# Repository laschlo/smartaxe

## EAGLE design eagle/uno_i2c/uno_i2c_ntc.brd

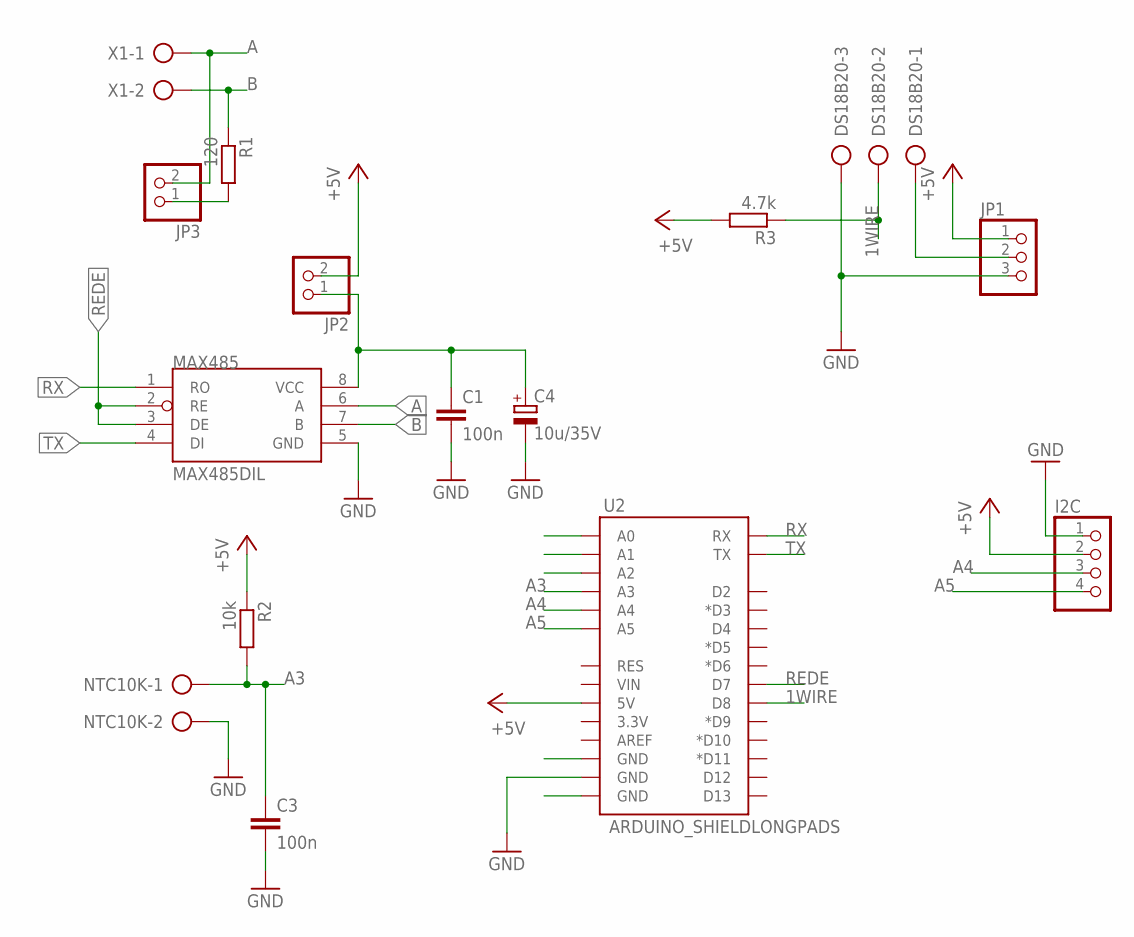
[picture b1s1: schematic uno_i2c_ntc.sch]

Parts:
C1, C3: 100n; C025-024X044
C4: 10u/35V; E2,5-5
DS18B20: AK500/3
I2C: PINHD-1X4/90; 1X04/90
JP1: PINHD-1X3; 1X03
JP2, JP3: PINHD-1X2; 1X02
MAX485: MAX485DIL; DIL08
NTC10K: AK500/2
R1: 120; 0207/10
R2: 10k; 0207/10
R3: 4.7k; 0207/10
U2: ARDUINO_SHIELDLONGPADS; DUEMILANOVE_SHIELD_LONGPADS
X1: AK500/2

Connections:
1WIRE: DS18B20.2, R3.1, U2.D8
+5V: I2C.2, JP1.1, JP2.2, R2.1, R3.2, U2.5V
A: JP3.2, MAX485.6 (A), X1.1
A0: U2.A0
A1: U2.A1
A2: U2.A2
A3: C3.1, NTC10K.1, R2.2, U2.A3
A4: I2C.3, U2.A4
A5: I2C.4, U2.A5
B: MAX485.7 (B), R1.1, X1.2
GND: C1.2, C3.2, C4.-, DS18B20.3, I2C.1, JP1.3, MAX485.5 (GND), NTC10K.2, U2.GND@0 (GND), U2.GND@1 (GND), U2.GND@2 (GND)
unnamed: JP3.1, R1.2
unnamed: DS18B20.1, JP1.2
unnamed: C1.1, C4.+, JP2.1, MAX485.8 (VCC)
REDE: MAX485.2 (RE), MAX485.3 (DE), U2.D7
RX: MAX485.1 (RO), U2.RX
TX: MAX485.4 (DI), U2.TX

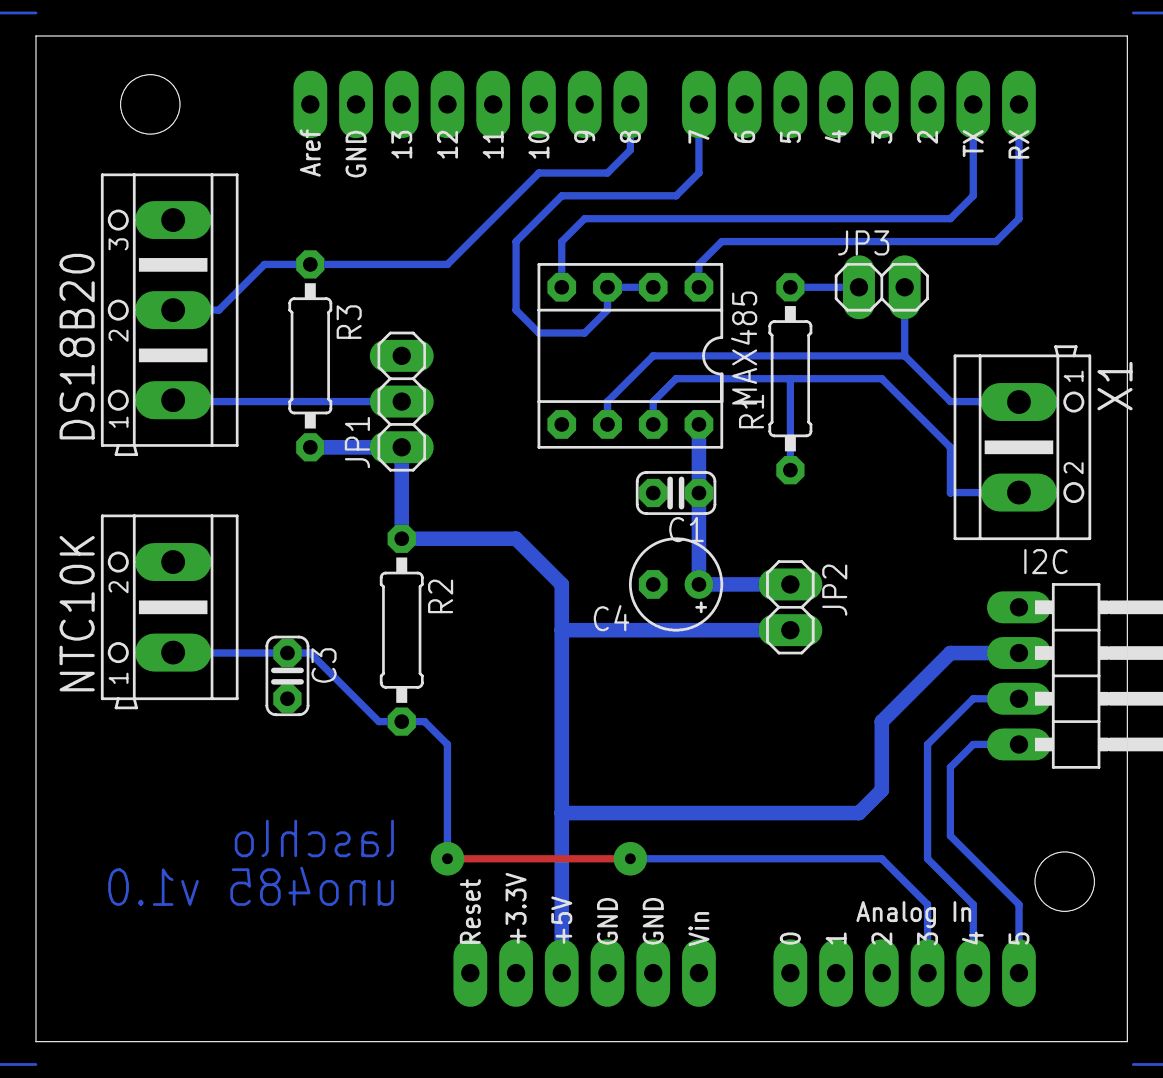
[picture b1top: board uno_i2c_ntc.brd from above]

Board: 2 copper layers, 60.6 x 55.9 mm, 15 parts (0 on the bottom side), 14 nets.

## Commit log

2014-02-26 firs commit
2014-02-26 adding libs
2014-02-26 adding project files
2014-02-26 adding project files for Atmel Studio
2014-02-28 small changes
2015-11-28 Added Atmel Studio projects
2015-12-02 cleanup
2015-12-02 GIT experiments
2015-12-27 Changed P_CO DELAYS
2015-12-28 simple change
2016-11-11 small updates
2016-11-11 Added new projects
2017-05-18 Eagle updates

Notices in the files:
parts and their libraries:
SparkFun-Boards: Licensing: CC v3.0 Share-Alike You are welcome to use this library for commercial purposes.
